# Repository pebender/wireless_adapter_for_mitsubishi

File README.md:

# A Wireless Adapter for a Mitsubishi Heat Pump Indoor Unit

This project is neither associated with nor endorsed by Mitsubishi Electric. By using this project, you may void your warranty or break your heat pump.

## The Wireless Adapter

The wireless adapter is a device for connecting an indoor unit of [our Mitsubishi Electric heat pump system](./docs/requirements.md#existing-system) to [our home automation system](./docs/background/automation.md). The wireless adapter is similar to [Mitsubishi Electric's PAC-USWHS002-WF-2 Wireless Interface 2](https://www.mitsubishipro.com/products/PAC-USWHS002-WF-2), except the wireless adapter is Open Source and doesn't depend on a cloud service.

The wireless adapter has three distinct parts

- the Open Source [hardware](./docs/hardware.md),
- the Open Source [enclosure](./docs/enclosure.md) and
- the Open Source [firmware](./docs/firmware.md).

### The Wireless Adapter Hardware

The [hardware](./docs/hardware.md) is likely both overly and poorly designed. Relative to many other people's designs, my design pays (more) attention to safety, including correct logic levels, safe power consumption and transient voltage suppression.

The hardware is a two-layer printed circuit board assembly (PCBA). I did the design and layout using the Open Source PCB design suite [KiCad](https://www.kicad.org). In addition, I did the step down power supply design using [Texas Instrument's WEBENCH&reg; Power Designer](https://webench.ti.com/power-designer/). I paid [JLCPCB](https://jlcpcb.com) to fabricate and assemble the hardware. I licensed the hardware design and layout under the [MIT license](./LICENSE.txt).

### The Wireless Adapter Enclosure

The [enclosure](./docs/enclosure.md) is likely overly conservative. I had no experience designing 3D printed enclosures, and I wanted to be sure the enclosure wasn't too fragile.

I did the enclosure design using the Open Source 3D parametric modeler [FreeCAD](https://www.freecad.org). I paid JLCPCB to 3D print the enclosure. I licensed the enclosure design under the MIT license.

### The Wireless Adapter Firmware

I contributed nothing to the [firmware](./docs/firmware.md). I built it from the Open Source [ESPHome](https://esphome.io) and the Open Source [mUART Project](https://muart-group.github.io)'s [mitsubishi_itp](https://github.com/muart-group/esphome-components) ESPHome component,

## The Motivation

I undertook this project because

- I needed a project,
- I wanted to learn what it takes to develop hardware today,
- I wanted to learn what it takes to develop enclosures, and
- I wasn't satisfied with our current solution for connecting the indoor units of our Mitsubishi Electric heat pump system to our home automation system. It depends on two [Honeywell THM6000R7001 RedLINK&reg; Internet Gateways](https://www.resideo.com/us/en/pro/products/air/thermostats/thermostat-accessories/redlinkr-internet-gateway-with-ethernet-cable-and-power-cord-thm6000r7001-u/) and the [Honeywell Home Total Connect Comfort](https://mytotalconnectcomfort.com) cloud. Because of its reliance on the RedLINK&reg; wireless protocol, it's relatively slow. In addition, because its reliance on the cloud it's relatively unreliable.

I wouldn't have undertaken this project had others not already done the work to connect their Mitsubishi Electric heat pumps to their home automation systems, including

- [Hadley Rich's hacking of his Mitsubishi heat pump)](https://nicegear.nz/blog/hacking-a-mitsubishi-heat-pump-air-conditioner/),
- [SwiCago's HeatPump software](https://github.com/SwiCago/HeatPump),
- [Geoff Davis (esphome-mitsubishiheatpump software)](https://github.com/geoffdavis/esphome-mitsubishiheatpump), and
- [the mUART project's software](https://muart-group.github.io).

In addition, I wouldn't have undertaken this project without the knowledge and confidence I gained as

- a high school student in [John McCollum](https://www.eetimes.com/john-mccollum-hs-teacher-taught-electronics-with-love/)'s electronics class at [Homestead High School](https://en.wikipedia.org/wiki/Homestead_High_School_(California)),
- a hardware intern at [NCR](https://www.ncr.com),
- a PhD student under [Jack Wolf](https://en.wikipedia.org/wiki/Jack_Wolf) at the [University of California San Diego (UCSD)](https://ucsd.edu), and
- a 20+ year employee at [Qualcomm](https://www.qualcomm.com).

Finally, I wouldn't have undertaken this project had an existing design contained

- a level shifter for the UART signals,
- a power module designed to meet the required efficiency and the EMI standards, and
- a reasonable level of Transient Voltage Suppression (TVS).

My [background](./docs/background.md) provides more insight into why I undertook this project.

## The Evolution

I didn't design the hardware and the enclosure as a unified project. Initially, I designed the hardware with the intent of using an off-the-shelf enclosure. So, I designed the hardware to fit in the off-the-shelf enclosure. However, I ran into problems mounting the hardware in the off-the-shelf enclosure as well as cutting the necessary openings in the off-the-shelf enclosure. So, I decided to make a custom enclosure. However, I already had the hardware fabricated and assembled. Therefore, I designed the enclosure around the existing hardware. Had I designed them together, both the hardware and the enclosure would have been different.

## References

[References](./docs/references.md)

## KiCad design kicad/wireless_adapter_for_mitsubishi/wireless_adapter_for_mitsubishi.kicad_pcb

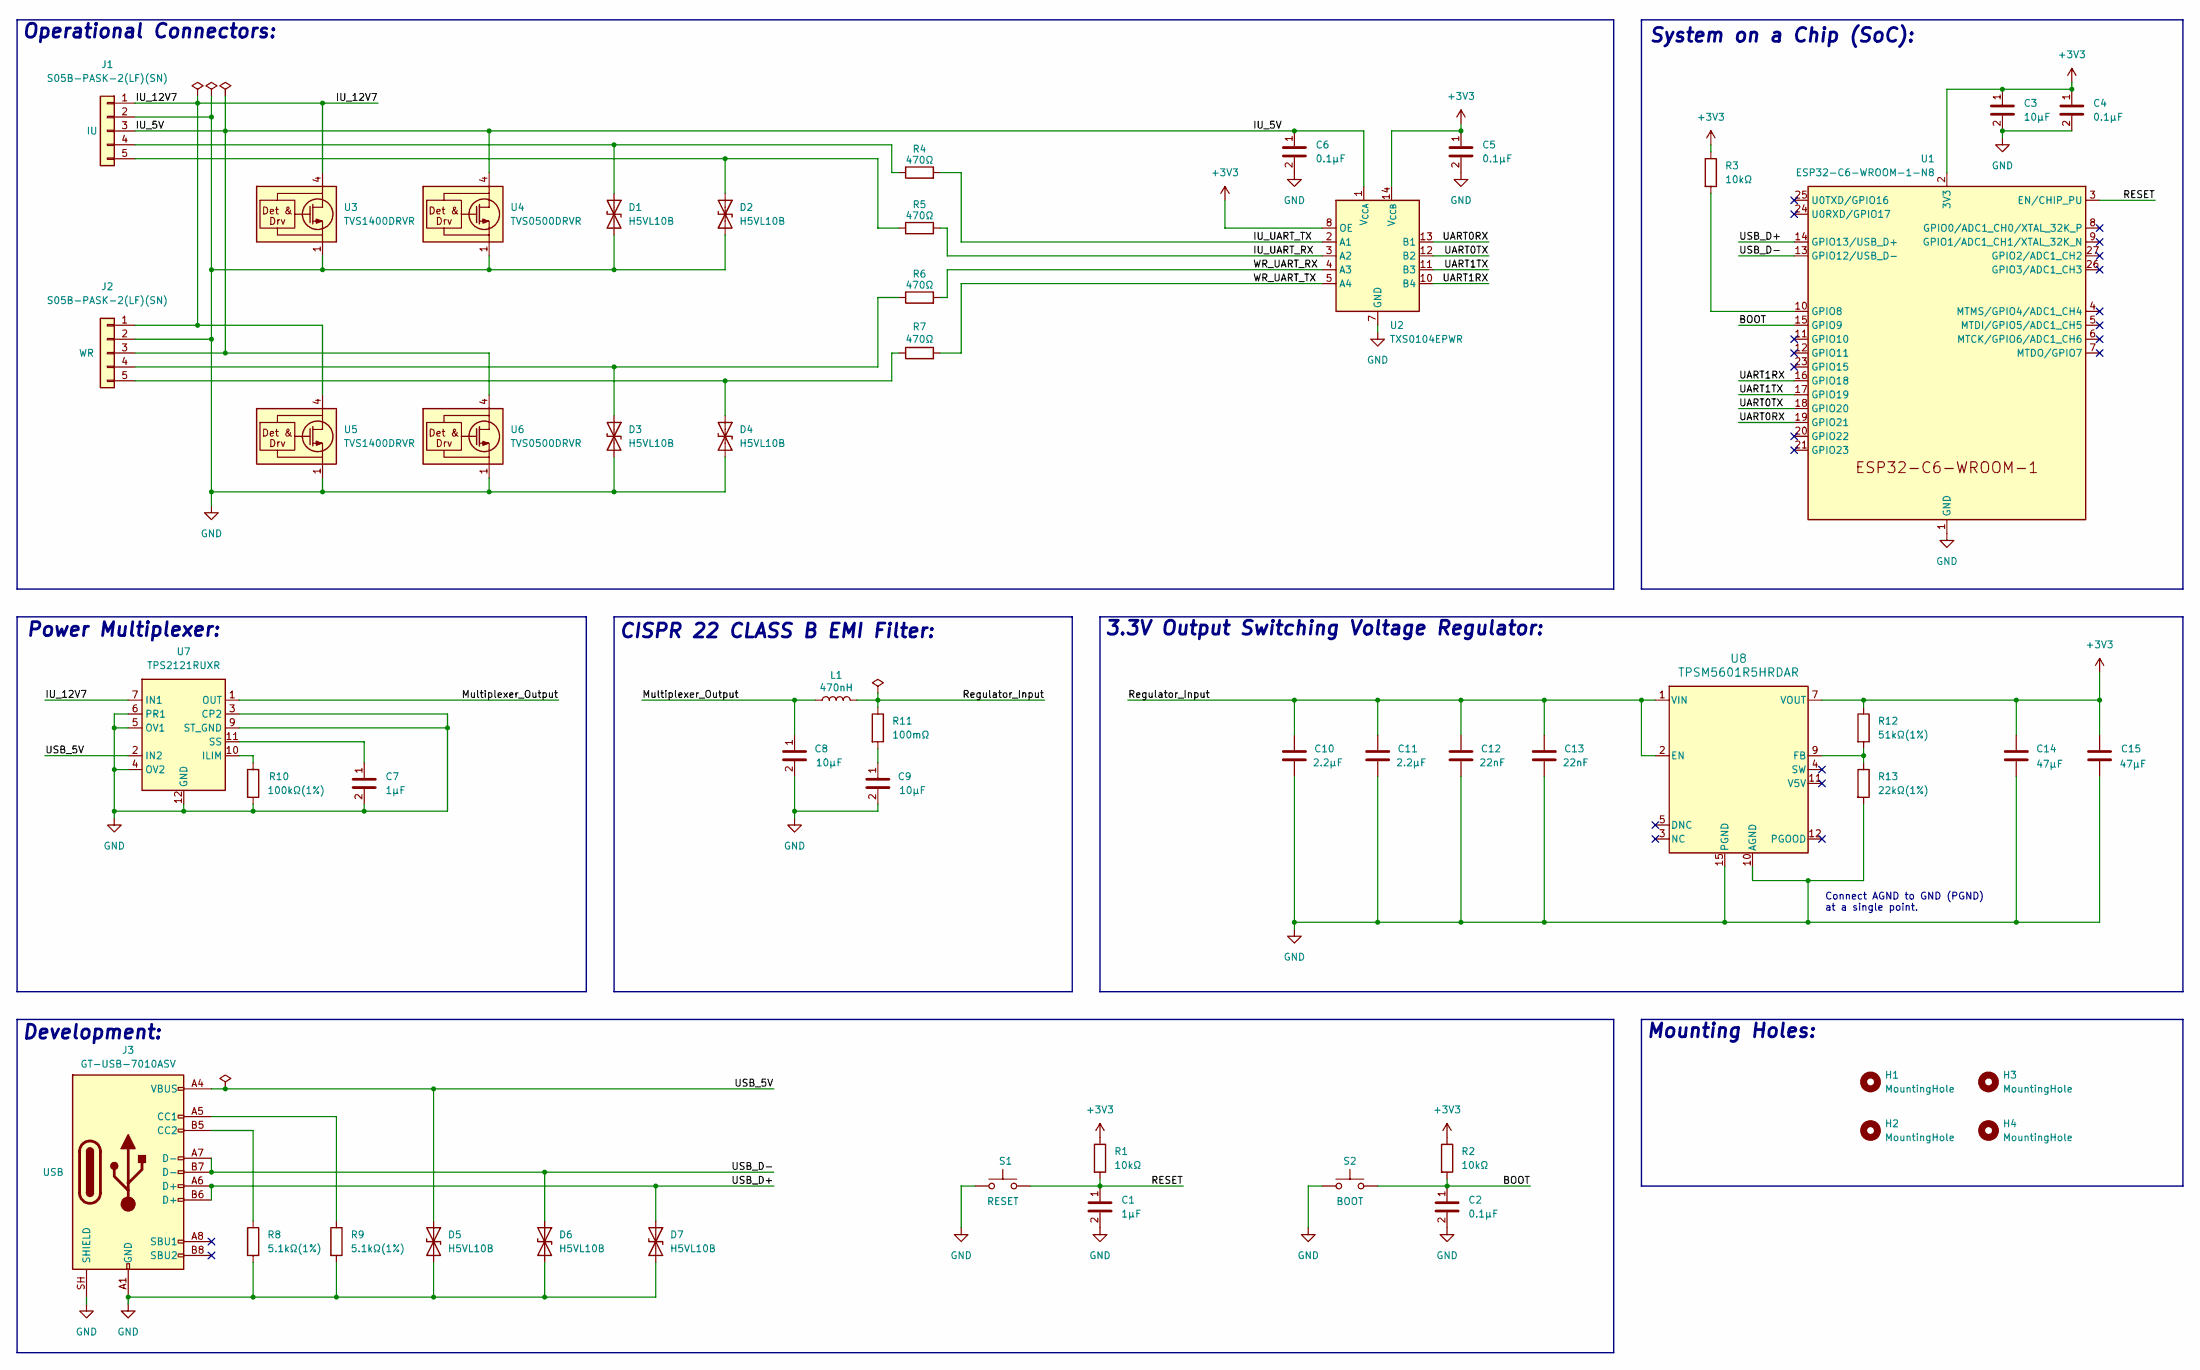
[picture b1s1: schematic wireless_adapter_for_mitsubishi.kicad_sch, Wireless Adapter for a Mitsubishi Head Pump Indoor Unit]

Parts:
C1, C7: 1μF; C_0402_1005Metric; Part CL05A105KA5NQNC; LCSC Part # C52923
C2, C4, C5, C6: 0.1μF; C_0402_1005Metric; Part CL05B104KO5NNNC; LCSC Part # C1525
C3, C8, C9: 10μF; C_1206_3216Metric; Part CL31A106KBHNNNE; LCSC Part # C13585
C10, C11: 2.2μF; C_1206_3216Metric; Part CL31B225KBHNNNE; LCSC Part # C50254
C12, C13: 22nF; C_0603_1608Metric; Part CL10B223KB8NNNC; LCSC Part # C21122
C14, C15: 47μF; C_1206_3216Metric; Part CL31A476MPHNNNE; LCSC Part # C96123
D1, D2, D3, D4, D5, D6, D7: H5VL10B; D_SOD-882; Part H5VL10B; LCSC Part # C7420372
H1, H2, H3, H4: MountingHole; MountingHole_3.2mm_M3
J1, J2: S05B-PASK-2(LF)(SN); JST_PA_S05B-PASK-2_1x05_P2.00mm_Horizontal; Part S05B-PASK-2(LF)(SN); LCSC Part # C489718
J3: GT-USB-7010ASV; USB_C_Receptacle_G-Switch_GT-USB-7010ASV; Part GT-USB-7010ASV; LCSC Part # C2988369
L1: 470nH; L_0806_2016Metric; Part DFE201610E-R47M=P2; LCSC Part # C269773
R1, R2, R3: 10kΩ; R_0402_1005Metric; Part 0402WGF1002TCE; LCSC Part # C25744
R4, R5, R6, R7: 470Ω; R_0402_1005Metric; Part 0402WGF4700TCE; LCSC Part # C25117
R8, R9: 5.1kΩ(1%); R_0402_1005Metric; Part 0402WGF4700TCE; LCSC Part # C25117
R10: 100kΩ(1%); R_0402_1005Metric; Part 0402WGF1003TCE; LCSC Part # C25741
R11: 100mΩ; R_1206_3216Metric; Part 1206W4F100LT5E; LCSC Part # C25334
R12: 51kΩ(1%); R_0402_1005Metric; Part 0402WGF5102TCE; LCSC Part # C25794
R13: 22kΩ(1%); R_0402_1005Metric; Part 0402WGF2202TCE; LCSC Part # C25768
S1, S2: SW_PUSH; SW_SPST_TS-1088-xR020; Part TS-1088-AR02016; LCSC Part # C720477
U1: ESP32-C6-WROOM-1-N8; ESP32-C6-WROOM-1; LCSC Part # C5366877
U2: TXS0104EPWR; TSSOP-14_4.4x5mm_P0.65mm; Part TXS0104EPWR; LCSC Part # C44955
U3, U5: TVS1400DRVR; WSON-6-1EP_2x2mm_P0.65mm_EP1x1.6mm; Part TVS1400DRVR; LCSC Part # C1975229
U4, U6: TVS0500DRVR; WSON-6-1EP_2x2mm_P0.65mm_EP1x1.6mm; Part TVS0500DRVR; LCSC Part # C609571
U7: TPS2121RUXR; Texas_RUX0012A_VQFN-HR-12_2x2.5x1mm_P0.5mm; Part TPS2121RUXT; LCSC Part # C2156025
U8: TPSM5601R5HRDAR; Texas_RDA0015A_B3QFN-14-1EP_5x5.5x4.1mm_P0.65mm; Part TPSM5601R5HRDAR; LCSC Part # C2846044

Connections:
+3V3: C3.1, C4.1, C5.1, C14.1, C15.1, R1.1, R2.1, R3.1, R12.1, U1.2 (3V3), U2.8 (OE), U2.14 (V_{CCB}), U8.7 (VOUT), U8.8 (VOUT)
/BOOT: C2.1, R2.2, S2.2, U1.15 (GPIO9)
/IU_5V: C6.1, J1.3, J2.3, U2.1 (V_{CCA}), U4.4 (IN), U4.5 (IN), U4.6 (IN), U6.4 (IN), U6.5 (IN), U6.6 (IN)
/IU_12V7: J1.1, J2.1, U3.4 (IN), U3.5 (IN), U3.6 (IN), U5.4 (IN), U5.5 (IN), U5.6 (IN), U7.7 (IN1)
/IU_UART_RX: R5.2, U2.3 (A2)
/IU_UART_TX: R4.2, U2.2 (A1)
/Multiplexer_Output: C8.1, L1.1, U7.1 (OUT), U7.8 (OUT)
/RESET: C1.1, R1.2, S1.2, U1.3 (EN/CHIP_PU)
/Regulator_Input: C10.1, C11.1, C12.1, C13.1, L1.2, R11.1, U8.1 (VIN), U8.2 (EN), U8.14 (VIN)
/UART0RX: U1.19 (GPIO21), U2.13 (B1)
/UART0TX: U1.18 (GPIO20), U2.12 (B2)
/UART1RX: U1.16 (GPIO18), U2.10 (B4)
/UART1TX: U1.17 (GPIO19), U2.11 (B3)
/USB_5V: D5.1 (A1), J3.A4 (VBUS), J3.A9 (VBUS), J3.B4 (VBUS), J3.B9 (VBUS), U7.2 (IN2)
/USB_D+: D7.1 (A1), J3.A6 (D+), J3.B6 (D+), U1.14 (GPIO13/USB_D+)
/USB_D-: D6.1 (A1), J3.A7 (D-), J3.B7 (D-), U1.13 (GPIO12/USB_D-)
/WR_UART_RX: R6.2, U2.4 (A3)
/WR_UART_TX: R7.2, U2.5 (A4)
GND: C1.2, C2.2, C3.2, C4.2, C5.2, C6.2, C7.2, C8.2, C9.2, C10.2, C11.2, C12.2, C13.2, C14.2, C15.2, D1.2 (A2), D2.2 (A2), D3.2 (A2), D4.2 (A2), D5.2 (A2), D6.2 (A2), D7.2 (A2), J1.2, J2.2, J3.A1 (GND), J3.A12 (GND), J3.B1 (GND), J3.B12 (GND), J3.SH (SHIELD), R8.2, R9.2, R10.2, R13.2, S1.1, S2.1, U1.1 (GND), U1.28 (GND), U1.29 (GND), U2.7 (GND), U3.1 (GND), U3.2 (GND), U3.3 (GND), U3.7 (GND), U4.1 (GND), U4.2 (GND), U4.3 (GND), U4.7 (GND), U5.1 (GND), U5.2 (GND), U5.3 (GND), U5.7 (GND), U6.1 (GND), U6.2 (GND), U6.3 (GND), U6.7 (GND), U7.3 (CP2), U7.4 (OV2), U7.5 (OV1), U7.6 (PR1), U7.9 (ST_GND), U7.12 (GND), U8.10 (AGND), U8.15 (PGND)
unnamed: C9.1, R11.2
unnamed: D1.1 (A1), J1.4, R4.1
unnamed: D2.1 (A1), J1.5, R5.1
unnamed: D3.1 (A1), J2.4, R6.1
unnamed: D4.1 (A1), J2.5, R7.1
unnamed: J3.A5 (CC1), R9.1
unnamed: J3.B5 (CC2), R8.1
unnamed: R3.2, U1.10 (GPIO8)
unnamed: R10.1, U7.10 (ILIM)
unnamed: C7.1, U7.11 (SS)
unnamed: R12.2, R13.1, U8.9 (FB)

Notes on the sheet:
Connect AGND to GND (PGND) at a single point.
System on a Chip (SoC):
Mounting Holes:
Operational Connectors:
3.3V Output Switching Voltage Regulator:
CISPR 22 CLASS B EMI Filter:
Power Multiplexer:
Development:

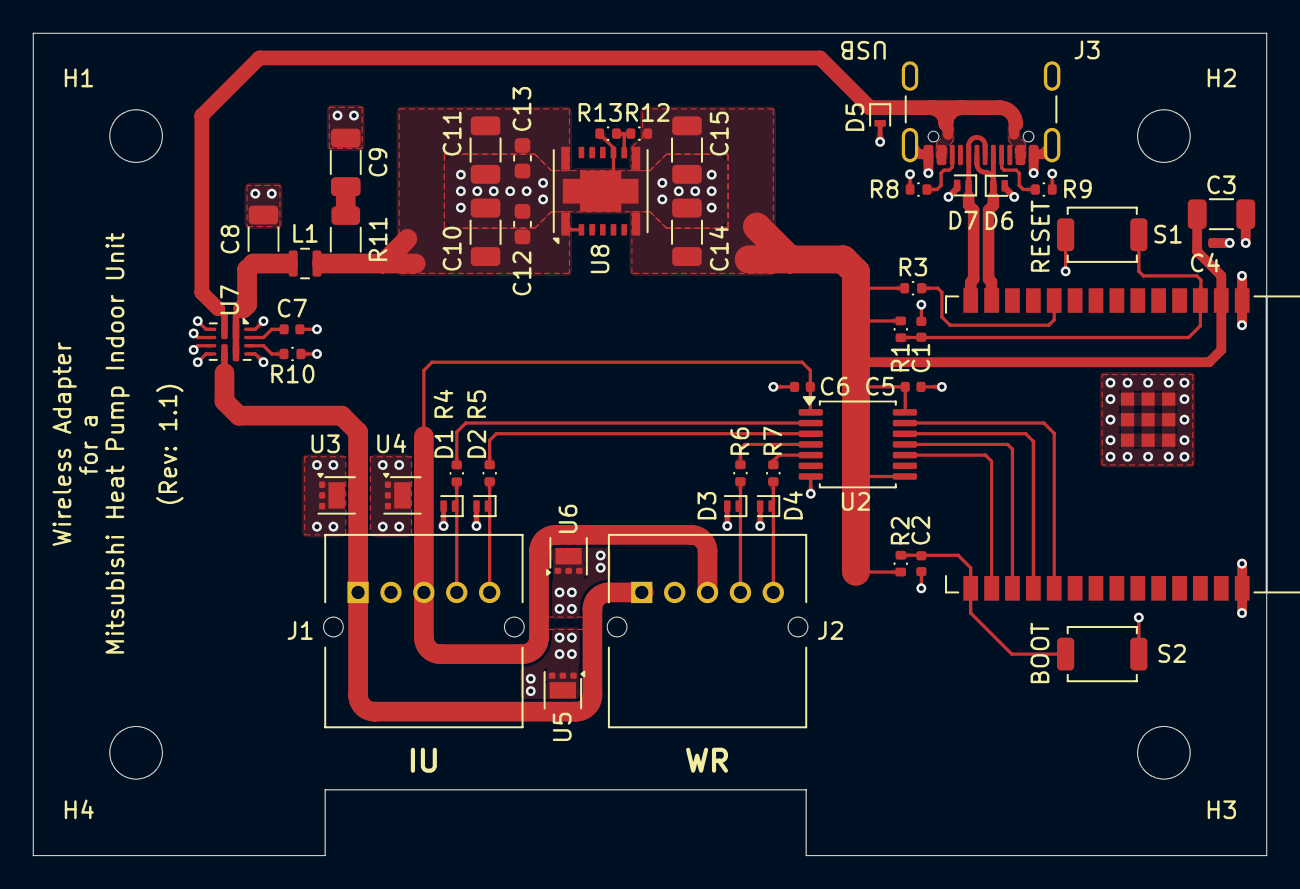
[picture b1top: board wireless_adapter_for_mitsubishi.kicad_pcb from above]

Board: 2 copper layers, 75.0 x 50.0 mm, 53 parts (0 on the bottom side), 30 nets.

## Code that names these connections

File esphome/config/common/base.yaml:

esphome:
  name: ${name}
  friendly_name: ${friendly_name}
  min_version: 2026.3.3

  on_boot:
    priority: 260
    then:
      - select.set:
          id: temperature_source_select
          option: "Thermostat"

esp32:
  variant: esp32c6
  flash_size: 8MB
  framework:
    type: esp-idf

external_components:
  - source: github://muart-group/esphome-components@main
    components: [ mitsubishi_itp ]

ota:
  - platform: esphome
    password: ${ota_password}

api:
  encryption:
    key: ${api_encryption_key}

time:
  - platform: homeassistant
    id: homeassistant_time

uart:
  - id: iu_uart
    baud_rate: 2400
    parity: EVEN
    rx_pin: GPIO21
    tx_pin: GPIO20
  - id: wr_uart
    baud_rate: 2400
    parity: EVEN
    rx_pin: GPIO18
    tx_pin: GPIO19

climate:
  - platform: mitsubishi_itp
    id: heat_pump
    name: "Thermostat"
    icon: mdi:heat-pump
    uart_heatpump: iu_uart
    uart_thermostat: wr_uart
    supported_modes:
      - 'OFF'
      - HEAT
      - COOL
      - FAN_ONLY
      - DRY
    supported_fan_modes:
      - AUTO
      - QUIET
      - LOW
      - MEDIUM
      - HIGH
    custom_fan_modes:
      - VERYHIGH
    # enhanced_mhk: True
    mhk_fahrenheit_correction: true
    visual:
      temperature_step:
        target_temperature: 1.0
        current_temperature: 1.0
    update_interval: 10s

select:
  - platform: mitsubishi_itp
    temperature_source:
      name: "Temperature Source"
      id: temperature_source_select
      sources: []
    vane_position:
      name: "Vane Position"
    horizontal_vane_position:
      name: "H. Vane Position"

text_sensor:
  - platform: mitsubishi_itp
    actual_fan:
      name: "Actual Fan"
    error_code:
      name: "Error Code"

# Default logging level
logger:
  baud_rate: 0
  level: DEBUG
  logs:
    EVT_SETS : DEBUG
    WIFI : INFO
    MQTT : INFO
    WRITE_SETTINGS : DEBUG
    SETTINGS : DEBUG
    STATUS : INFO
    CN105Climate: WARN
    CN105: DEBUG
    climate: WARN
    sensor: WARN
    chkSum : INFO
    WRITE : WARN
    READ : WARN
    Header: INFO
    Decoder : DEBUG
    CONTROL_WANTED_SETTINGS: DEBUG

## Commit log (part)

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2026-04-12 Clean up documentation.
2026-04-12 Fix license file name.
2026-04-13 Rename some of the KiCad sheets.
2026-04-13 Fix the name of a KiCad sheet.
2026-04-13 Rename some KiCad buses.
2026-04-14 Clean up KiCad schematic.
2026-04-15 Flatten KiCad schematic.
2026-04-17 Update PCBA STEP file.
2026-04-20 Add configuration for Jekyll site
2026-04-20 Clean up KiCad schematic. Improve grounding in on PCB.
2026-04-23 Improve USB differential routing.
2026-05-05 Fix problem with thread support.
2026-05-21 Switch to using main branch of muart.
